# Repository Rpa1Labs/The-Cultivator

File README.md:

# The Cultivator

## INSTALLATION

---
### Nvidia Jetson Nano

---

Programmes requis:
```
g++
python3
python2
sudo

python2-pip
python3-pip
```

Librairies python 3 requises:
```
python-socketio
board
adafruit_bme680
adafruit_seesaw
```

Librairies python 2 requises:
```
cv2
```

Librairies C++ requises:
```
JetsonGPIO.h
```

Dans le dossier `Jetson`, copiez le fichier `config-sample.json` et renommez-le en `config.json`

Complétez le fichier `config.json` avec les informations suivantes:
 - l'url de votre serveur web. Exemple : `http://127.0.0.1:5000`

Exécutez la commande suivante dans le dossier Jetson:
```sh
./install.sh
```

---

## Serveur Web

---

Programmes requis:
```
python3
screen
influxdb
sudo

python3-pip
```

Librairies python 3 requises:
```
influxdb_client
flask-socketio
flask
sqlite3
```

Sur influxdb, créez les buckets suivants:
```
Environnement_measures
Image
```

Ensuite, récupérez la clé API de votre compte influxdb

Dans le dossier `flask-server`, copiez le fichier `config-sample.json` et renommez-le en `config.json`

Complétez le fichier `config.json` avec les informations suivantes:
 - la clé API de votre base InfluxDB (token)
 - l'url de votre base InfluxDB
 - le nom de l'organisation de votre base InfluxDB

Enfin, exécutez les commandes suivantes dans le dossier flask-server afin de démarrer le serveur:
```sh
screen
sudo python3 serveur.py
```

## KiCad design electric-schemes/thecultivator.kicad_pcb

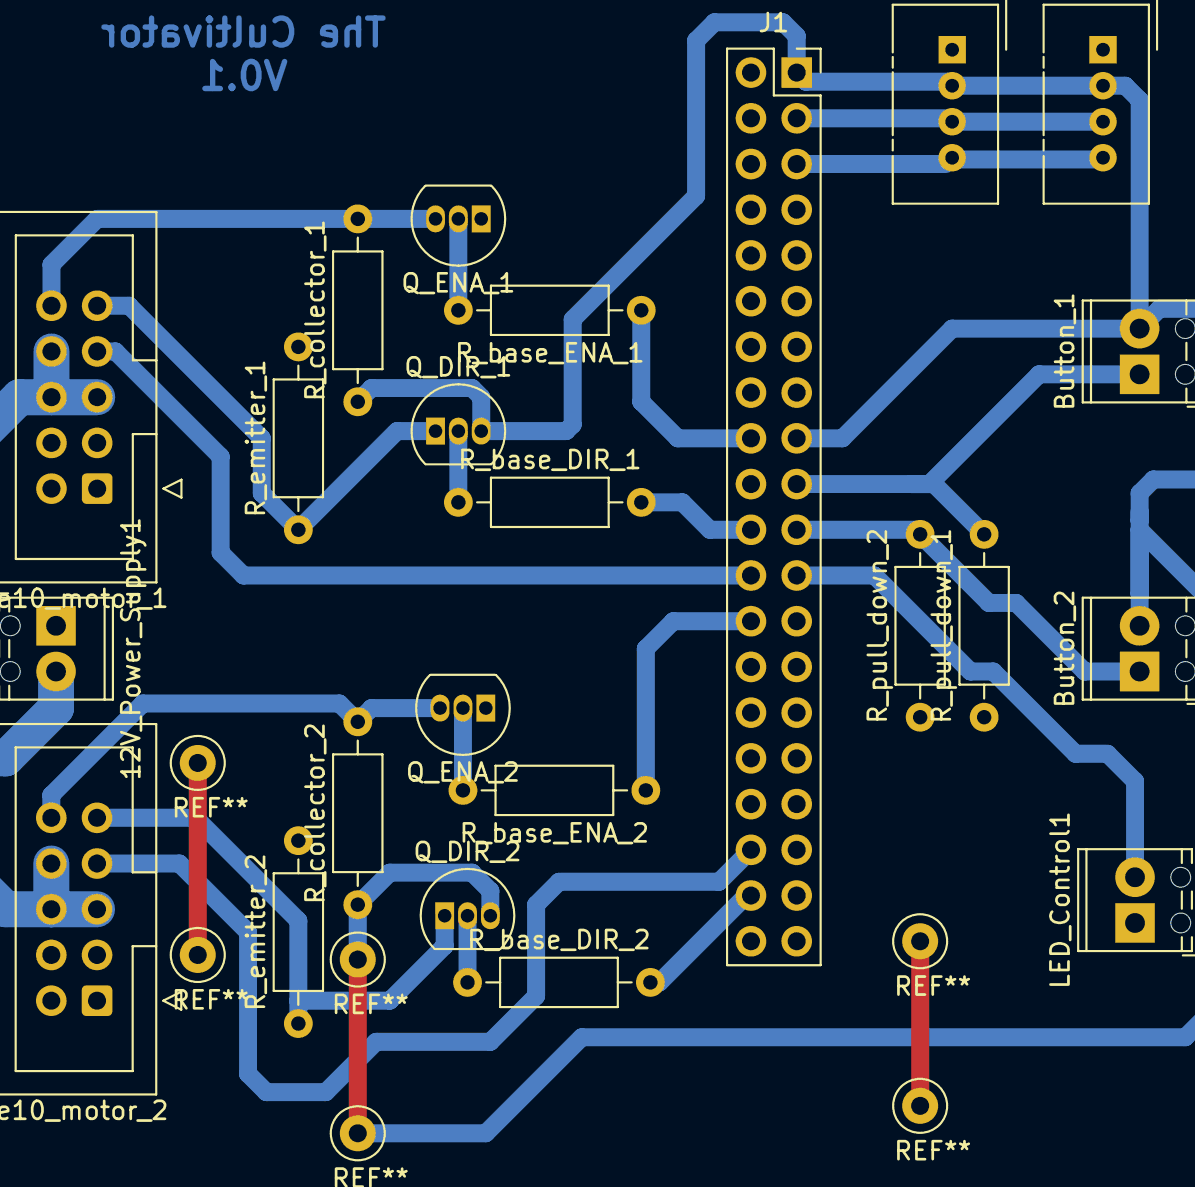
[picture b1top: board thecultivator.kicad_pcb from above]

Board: 2 copper layers, 23 parts (0 on the bottom side), 22 nets.

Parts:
12V_Power_Supply1: Screw_Terminal_01x02; TerminalBlock_Phoenix_MPT-0,5-2-2.54_1x02_P2.54mm_Horizontal
Adafruit_STEMMA1: Conn_01x04; NS-Tech_Grove_1x04_P2mm_Vertical
BME680: Conn_01x04; NS-Tech_Grove_1x04_P2mm_Vertical
Button_1, Button_2: Screw_Terminal_01x02; TerminalBlock_Phoenix_MPT-0,5-2-2.54_1x02_P2.54mm_Horizontal
J1: Raspberry_Pi_2_3; PinSocket_2x20_P2.54mm_Vertical
LED_Control1: Screw_Terminal_01x02; TerminalBlock_Phoenix_MPT-0,5-2-2.54_1x02_P2.54mm_Horizontal
Q_DIR_1, Q_DIR_2: PN2222A; TO-92_Inline
Q_ENA_1, Q_ENA_2: PN2222A; TO-92_Inline
R_base_DIR_1, R_base_DIR_2: 10k; R_Axial_DIN0207_L6.3mm_D2.5mm_P10.16mm_Horizontal
R_base_ENA_1, R_base_ENA_2: 10k; R_Axial_DIN0207_L6.3mm_D2.5mm_P10.16mm_Horizontal
R_collector_1, R_collector_2: 1k; R_Axial_DIN0207_L6.3mm_D2.5mm_P10.16mm_Horizontal
R_emitter_1, R_emitter_2: 2k; R_Axial_DIN0207_L6.3mm_D2.5mm_P10.16mm_Horizontal
R_pull_down_1, R_pull_down_2: 2k; R_Axial_DIN0207_L6.3mm_D2.5mm_P10.16mm_Horizontal
he10_motor_1, he10_motor_2: Conn_02x05_Counter_Clockwise; IDC-Header_2x05_P2.54mm_Vertical

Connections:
+3V3: Adafruit_STEMMA1.2, BME680.2, Button_1.2, Button_2.2, J1.1 (3V3), J1.17 (3V3), Q_DIR_1.3 (C), Q_DIR_2.3 (C), R_collector_1.1, R_collector_2.1
+12V: 12V_Power_Supply1.2, he10_motor_1.5, he10_motor_1.6, he10_motor_1.8, he10_motor_2.5, he10_motor_2.6, he10_motor_2.8
/Out_Dir_1: Q_DIR_1.1 (E), R_emitter_1.1, he10_motor_1.9
/Out_Dir_2: Q_DIR_2.1 (E), R_emitter_2.1, he10_motor_2.9
/Out_Ena_1: Q_ENA_1.3 (C), R_collector_1.2, he10_motor_1.10
/Out_Ena_2: Q_ENA_2.3 (C), R_collector_2.2, he10_motor_2.10
/Pin_Pull_1: J1.24 (~CE0/GPIO8), he10_motor_1.7
/Pin_Pull_2: J1.36 (GPIO16), he10_motor_2.7
GND: 12V_Power_Supply1.1, Adafruit_STEMMA1.1, BME680.1, J1.25 (GND), J1.30 (GND), J1.34 (GND), J1.39 (GND), LED_Control1.1, Q_ENA_1.1 (E), Q_ENA_2.1 (E), R_emitter_1.2, R_emitter_2.2, R_pull_down_1.1, R_pull_down_2.1, he10_motor_1.1, he10_motor_1.2, he10_motor_1.3, he10_motor_1.4, he10_motor_2.1, he10_motor_2.2, he10_motor_2.3, he10_motor_2.4
unnamed: Adafruit_STEMMA1.3, BME680.3, J1.3 (SDA/GPIO2)
unnamed: Adafruit_STEMMA1.4, BME680.4, J1.5 (SCL/GPIO3)
unnamed: Button_1.1, J1.19 (MOSI0/GPIO10), R_pull_down_1.2
unnamed: Button_2.1, J1.21 (MISO0/GPIO9), R_pull_down_2.2
unnamed: J1.18 (GPIO24), R_base_ENA_1.1
unnamed: J1.22 (GPIO25), R_base_DIR_1.2
unnamed: J1.23 (SCLK0/GPIO11), LED_Control1.2
unnamed: J1.26 (~CE1/GPIO7), R_base_ENA_2.1
unnamed: J1.38 (GPIO20/MOSI1), R_base_DIR_2.2
unnamed: Q_DIR_1.2 (B), R_base_DIR_1.1
unnamed: Q_DIR_2.2 (B), R_base_DIR_2.1
unnamed: Q_ENA_1.2 (B), R_base_ENA_1.2
unnamed: Q_ENA_2.2 (B), R_base_ENA_2.2

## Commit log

2022-05-02 Ajout d'une partie du code de la Jetson
2022-05-02 Ajout du serveur web
2022-05-04 Ajout des features du client web
2022-05-07 Mise en place de l'exécution au démarrage + nettoyage code
2022-05-11 Ajout de tous les programmes
2022-05-20 Ajout du schéma électrique + PCB
2022-05-20 ajout AR
2022-05-28 Ajout de la vidéo de présentation
